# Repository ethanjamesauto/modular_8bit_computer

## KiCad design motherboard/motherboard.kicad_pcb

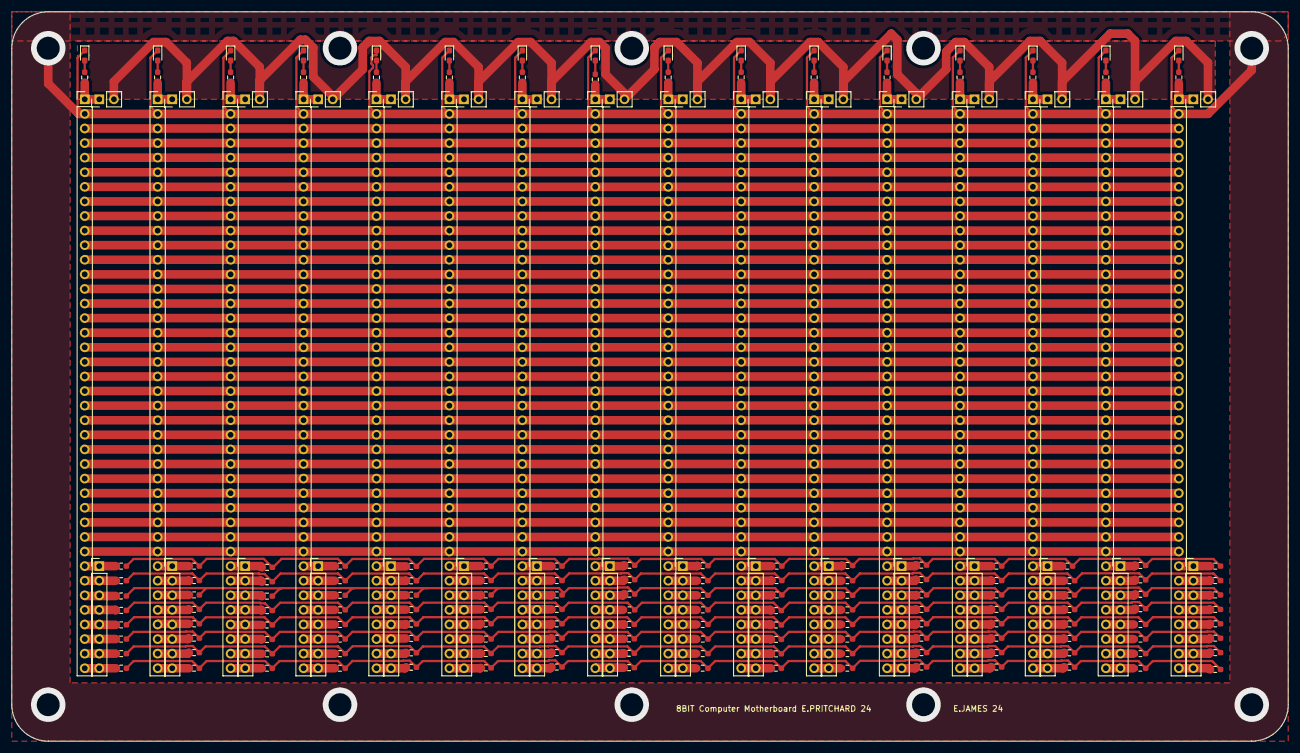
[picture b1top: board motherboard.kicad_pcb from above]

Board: 2 copper layers, 222.3 x 127.0 mm, 208 parts (0 on the bottom side), 200 nets.

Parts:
D1, D2, D3, D4, D5, D6, D7, D8, D9, D10, D11, D12, D13, D14, D15, D16: A0; LED_0603_1608Metric_Pad1.05x0.95mm_HandSolder
J1, J2, J5, J7, J9, J11, J13, J15, J17, J19, J21, J23, J25, J27, J29, J31: Conn_01x40_Pin; PinHeader_1x40_P2.54mm_Vertical
J3, J4, J6, J8, J10, J12, J14, J16, J18, J20, J22, J24, J26, J28, J30, J32: Conn_01x08_Pin; PinHeader_1x08_P2.54mm_Vertical
J33, J34, J35, J36, J37, J38, J39, J40, J41, J42, J43, J44, J45, J46, J47, J48: Conn_01x02_Pin; PinHeader_1x02_P2.54mm_Vertical
r1, r2, r3, r4, r5, r6, r7, r8, r9, r10, r11, r12, r13, r14, r15, r16, r17, r18, r19, r20, r21, r22, r23, r24, r25, r26, r27, r28, r29, r30, r31, r32, r33, r34, r35, r36, r37, r38, r39, r40, r41, r42, r43, r44, r45, r46, r47, r48, r49, r50, r51, r52, r53, r54, r55, r56, r57, r58, r59, r60, r61, r62, r63, r64, r65, r66, r67, r68, r69, r70, r71, r72, r73, r74, r75, r76, r77, r78, r79, r80, r81, r82, r83, r84, r85, r86, r87, r88, r89, r90, r91, r92, r93, r94, r95, r96, r97, r98, r99, r100, r101, r102, r103, r104, r105, r106, r107, r108, r109, r110, r111, r112, r113, r114, r115, r116, r117, r118, r119, r120, r121, r122, r123, r124, r125, r126, r127, r128, r129, r130, r131, r132, r133, r134, r135, r136, r137, r138, r139, r140, r141, r142, r143, r144: 470; R_0603_1608Metric_Pad0.98x0.95mm_HandSolder

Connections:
/5V_rawA: J2.1, J33.1, r1.2
/5V_rawB: J1.1, J34.1, r10.2
/5V_rawC: J5.1, J35.1, r19.2
/5V_rawD: J7.1, J36.1, r28.2
/5V_rawE: J9.1, J37.1, r37.2
/5V_rawF: J11.1, J38.1, r46.2
/5V_rawG: J13.1, J39.1, r55.2
/5V_rawH: J15.1, J40.1, r64.2
/5V_rawJ: J17.1, J41.1, r73.2
/5V_rawK: J19.1, J42.1, r82.2
/5V_rawL: J21.1, J43.1, r91.2
/5V_rawM: J23.1, J44.1, r100.2
/5V_rawN: J25.1, J45.1, r109.2
/5V_rawO: J27.1, J46.1, r118.2
/5V_rawP: J29.1, J47.1, r127.2
/5V_rawQ: J31.1, J48.1, r136.2
/A: J1.5, J2.5, J5.5, J7.5, J9.5, J11.5, J13.5, J15.5, J17.5, J19.5, J21.5, J23.5, J25.5, J27.5, J29.5, J31.5
/Addr_0_LSB: J1.17, J2.17, J5.17, J7.17, J9.17, J11.17, J13.17, J15.17, J17.17, J19.17, J21.17, J23.17, J25.17, J27.17, J29.17, J31.17
/Addr_1: J1.18, J2.18, J5.18, J7.18, J9.18, J11.18, J13.18, J15.18, J17.18, J19.18, J21.18, J23.18, J25.18, J27.18, J29.18, J31.18
/Addr_2: J1.19, J2.19, J5.19, J7.19, J9.19, J11.19, J13.19, J15.19, J17.19, J19.19, J21.19, J23.19, J25.19, J27.19, J29.19, J31.19
/Addr_3: J1.20, J2.20, J5.20, J7.20, J9.20, J11.20, J13.20, J15.20, J17.20, J19.20, J21.20, J23.20, J25.20, J27.20, J29.20, J31.20
/Addr_4: J1.21, J2.21, J5.21, J7.21, J9.21, J11.21, J13.21, J15.21, J17.21, J19.21, J21.21, J23.21, J25.21, J27.21, J29.21, J31.21
/Addr_5: J1.22, J2.22, J5.22, J7.22, J9.22, J11.22, J13.22, J15.22, J17.22, J19.22, J21.22, J23.22, J25.22, J27.22, J29.22, J31.22
/Addr_6: J1.23, J2.23, J5.23, J7.23, J9.23, J11.23, J13.23, J15.23, J17.23, J19.23, J21.23, J23.23, J25.23, J27.23, J29.23, J31.23
/Addr_7: J1.24, J2.24, J5.24, J7.24, J9.24, J11.24, J13.24, J15.24, J17.24, J19.24, J21.24, J23.24, J25.24, J27.24, J29.24, J31.24
/Addr_8: J1.25, J2.25, J5.25, J7.25, J9.25, J11.25, J13.25, J15.25, J17.25, J19.25, J21.25, J23.25, J25.25, J27.25, J29.25, J31.25
/Addr_9: J1.26, J2.26, J5.26, J7.26, J9.26, J11.26, J13.26, J15.26, J17.26, J19.26, J21.26, J23.26, J25.26, J27.26, J29.26, J31.26
/Addr_10: J1.27, J2.27, J5.27, J7.27, J9.27, J11.27, J13.27, J15.27, J17.27, J19.27, J21.27, J23.27, J25.27, J27.27, J29.27, J31.27
/Addr_11: J1.28, J2.28, J5.28, J7.28, J9.28, J11.28, J13.28, J15.28, J17.28, J19.28, J21.28, J23.28, J25.28, J27.28, J29.28, J31.28
/Addr_12: J1.29, J2.29, J5.29, J7.29, J9.29, J11.29, J13.29, J15.29, J17.29, J19.29, J21.29, J23.29, J25.29, J27.29, J29.29, J31.29
/Addr_13: J1.30, J2.30, J5.30, J7.30, J9.30, J11.30, J13.30, J15.30, J17.30, J19.30, J21.30, J23.30, J25.30, J27.30, J29.30, J31.30
/Addr_14: J1.31, J2.31, J5.31, J7.31, J9.31, J11.31, J13.31, J15.31, J17.31, J19.31, J21.31, J23.31, J25.31, J27.31, J29.31, J31.31
/Addr_15_MSB: J1.32, J2.32, J5.32, J7.32, J9.32, J11.32, J13.32, J15.32, J17.32, J19.32, J21.32, J23.32, J25.32, J27.32, J29.32, J31.32
/Aux_Bus_0_LSB: r2.1, r11.1, r20.1, r29.1, r38.1, r47.1, r56.1, r65.1, r74.1, r83.1, r92.1, r101.1, r110.1, r119.1, r128.1, r137.1
/Aux_Bus_1: r3.1, r12.1, r21.1, r30.1, r39.1, r48.1, r57.1, r66.1, r75.1, r84.1, r93.1, r102.1, r111.1, r120.1, r129.1, r138.1
/Aux_Bus_2: r4.1, r13.1, r22.1, r31.1, r40.1, r49.1, r58.1, r67.1, r76.1, r85.1, r94.1, r103.1, r112.1, r121.1, r130.1, r139.1
/Aux_Bus_3: r5.1, r14.1, r23.1, r32.1, r41.1, r50.1, r59.1, r68.1, r77.1, r86.1, r95.1, r104.1, r113.1, r122.1, r131.1, r140.1
/Aux_Bus_4: r6.1, r15.1, r24.1, r33.1, r42.1, r51.1, r60.1, r69.1, r78.1, r87.1, r96.1, r105.1, r114.1, r123.1, r132.1, r141.1
/Aux_Bus_5: r7.1, r16.1, r25.1, r34.1, r43.1, r52.1, r61.1, r70.1, r79.1, r88.1, r97.1, r106.1, r115.1, r124.1, r133.1, r142.1
/Aux_Bus_6: r8.1, r17.1, r26.1, r35.1, r44.1, r53.1, r62.1, r71.1, r80.1, r89.1, r98.1, r107.1, r116.1, r125.1, r134.1, r143.1
/Aux_Bus_7_MSB: r9.1, r18.1, r27.1, r36.1, r45.1, r54.1, r63.1, r72.1, r81.1, r90.1, r99.1, r108.1, r117.1, r126.1, r135.1, r144.1
/B: J1.6, J2.6, J5.6, J7.6, J9.6, J11.6, J13.6, J15.6, J17.6, J19.6, J21.6, J23.6, J25.6, J27.6, J29.6, J31.6
/C: J1.7, J2.7, J5.7, J7.7, J9.7, J11.7, J13.7, J15.7, J17.7, J19.7, J21.7, J23.7, J25.7, J27.7, J29.7, J31.7
/D: J1.8, J2.8, J5.8, J7.8, J9.8, J11.8, J13.8, J15.8, J17.8, J19.8, J21.8, J23.8, J25.8, J27.8, J29.8, J31.8
/Data_Bus_0_LSB: J1.9, J2.9, J5.9, J7.9, J9.9, J11.9, J13.9, J15.9, J17.9, J19.9, J21.9, J23.9, J25.9, J27.9, J29.9, J31.9
/Data_Bus_1: J1.10, J2.10, J5.10, J7.10, J9.10, J11.10, J13.10, J15.10, J17.10, J19.10, J21.10, J23.10, J25.10, J27.10, J29.10, J31.10
/Data_Bus_2: J1.11, J2.11, J5.11, J7.11, J9.11, J11.11, J13.11, J15.11, J17.11, J19.11, J21.11, J23.11, J25.11, J27.11, J29.11, J31.11
/Data_Bus_3: J1.12, J2.12, J5.12, J7.12, J9.12, J11.12, J13.12, J15.12, J17.12, J19.12, J21.12, J23.12, J25.12, J27.12, J29.12, J31.12
/Data_Bus_4: J1.13, J2.13, J5.13, J7.13, J9.13, J11.13, J13.13, J15.13, J17.13, J19.13, J21.13, J23.13, J25.13, J27.13, J29.13, J31.13
/Data_Bus_5: J1.14, J2.14, J5.14, J7.14, J9.14, J11.14, J13.14, J15.14, J17.14, J19.14, J21.14, J23.14, J25.14, J27.14, J29.14, J31.14
/Data_Bus_6: J1.15, J2.15, J5.15, J7.15, J9.15, J11.15, J13.15, J15.15, J17.15, J19.15, J21.15, J23.15, J25.15, J27.15, J29.15, J31.15
/Data_Bus_7_MSB: J1.16, J2.16, J5.16, J7.16, J9.16, J11.16, J13.16, J15.16, J17.16, J19.16, J21.16, J23.16, J25.16, J27.16, J29.16, J31.16
/clk: J1.3, J2.3, J5.3, J7.3, J9.3, J11.3, J13.3, J15.3, J17.3, J19.3, J21.3, J23.3, J25.3, J27.3, J29.3, J31.3
/reset_n: J1.4, J2.4, J5.4, J7.4, J9.4, J11.4, J13.4, J15.4, J17.4, J19.4, J21.4, J23.4, J25.4, J27.4, J29.4, J31.4
GND: D1.1 (K), D2.1 (K), D3.1 (K), D4.1 (K), D5.1 (K), D6.1 (K), D7.1 (K), D8.1 (K), D9.1 (K), D10.1 (K), D11.1 (K), D12.1 (K), D13.1 (K), D14.1 (K), D15.1 (K), D16.1 (K), J1.2, J2.2, J5.2, J7.2, J9.2, J11.2, J13.2, J15.2, J17.2, J19.2, J21.2, J23.2, J25.2, J27.2, J29.2, J31.2
unnamed: D1.2 (A), r1.1
unnamed: D2.2 (A), r10.1
unnamed: D3.2 (A), r19.1
unnamed: D4.2 (A), r28.1
unnamed: D5.2 (A), r37.1
unnamed: D6.2 (A), r46.1
unnamed: D7.2 (A), r55.1
unnamed: D8.2 (A), r64.1
unnamed: D9.2 (A), r73.1
unnamed: D10.2 (A), r82.1
unnamed: D11.2 (A), r91.1
unnamed: D12.2 (A), r100.1
unnamed: D13.2 (A), r109.1
unnamed: D14.2 (A), r118.1
unnamed: D15.2 (A), r127.1
unnamed: D16.2 (A), r136.1
unnamed: J1.33, J3.1, r11.2
unnamed: J1.34, J3.2, r12.2
unnamed: J1.35, J3.3, r13.2
unnamed: J1.36, J3.4, r14.2
unnamed: J1.37, J3.5, r15.2
unnamed: J1.38, J3.6, r16.2
unnamed: J1.39, J3.7, r17.2
unnamed: J1.40, J3.8, r18.2
unnamed: J2.33, J4.1, r2.2
unnamed: J2.34, J4.2, r3.2
unnamed: J2.35, J4.3, r4.2
unnamed: J2.36, J4.4, r5.2
unnamed: J2.37, J4.5, r6.2
unnamed: J2.38, J4.6, r7.2
unnamed: J2.39, J4.7, r8.2
unnamed: J2.40, J4.8, r9.2
unnamed: J5.33, J6.1, r20.2
unnamed: J5.34, J6.2, r21.2
unnamed: J5.35, J6.3, r22.2
unnamed: J5.36, J6.4, r23.2
unnamed: J5.37, J6.5, r24.2
unnamed: J5.38, J6.6, r25.2
unnamed: J5.39, J6.7, r26.2
unnamed: J5.40, J6.8, r27.2
unnamed: J7.33, J8.1, r29.2
unnamed: J7.34, J8.2, r30.2
unnamed: J7.35, J8.3, r31.2
unnamed: J7.36, J8.4, r32.2
unnamed: J7.37, J8.5, r33.2
unnamed: J7.38, J8.6, r34.2
unnamed: J7.39, J8.7, r35.2
unnamed: J7.40, J8.8, r36.2
unnamed: J9.33, J10.1, r38.2
unnamed: J9.34, J10.2, r39.2
unnamed: J9.35, J10.3, r40.2
unnamed: J9.36, J10.4, r41.2
unnamed: J9.37, J10.5, r42.2
unnamed: J9.38, J10.6, r43.2
unnamed: J9.39, J10.7, r44.2
unnamed: J9.40, J10.8, r45.2
unnamed: J11.33, J12.1, r47.2
unnamed: J11.34, J12.2, r48.2
unnamed: J11.35, J12.3, r49.2
unnamed: J11.36, J12.4, r50.2
unnamed: J11.37, J12.5, r51.2
unnamed: J11.38, J12.6, r52.2
unnamed: J11.39, J12.7, r53.2
unnamed: J11.40, J12.8, r54.2
unnamed: J13.33, J14.1, r56.2
unnamed: J13.34, J14.2, r57.2
unnamed: J13.35, J14.3, r58.2
unnamed: J13.36, J14.4, r59.2
unnamed: J13.37, J14.5, r60.2
unnamed: J13.38, J14.6, r61.2
unnamed: J13.39, J14.7, r62.2
unnamed: J13.40, J14.8, r63.2
unnamed: J15.33, J16.1, r65.2
unnamed: J15.34, J16.2, r66.2
unnamed: J15.35, J16.3, r67.2
unnamed: J15.36, J16.4, r68.2
unnamed: J15.37, J16.5, r69.2
unnamed: J15.38, J16.6, r70.2
unnamed: J15.39, J16.7, r71.2
unnamed: J15.40, J16.8, r72.2
unnamed: J17.33, J18.1, r74.2
unnamed: J17.34, J18.2, r75.2
unnamed: J17.35, J18.3, r76.2
unnamed: J17.36, J18.4, r77.2
unnamed: J17.37, J18.5, r78.2
unnamed: J17.38, J18.6, r79.2
unnamed: J17.39, J18.7, r80.2
unnamed: J17.40, J18.8, r81.2
unnamed: J19.33, J20.1, r83.2
unnamed: J19.34, J20.2, r84.2
unnamed: J19.35, J20.3, r85.2
unnamed: J19.36, J20.4, r86.2
unnamed: J19.37, J20.5, r87.2
unnamed: J19.38, J20.6, r88.2
unnamed: J19.39, J20.7, r89.2
unnamed: J19.40, J20.8, r90.2
unnamed: J21.33, J22.1, r92.2
unnamed: J21.34, J22.2, r93.2
unnamed: J21.35, J22.3, r94.2
unnamed: J21.36, J22.4, r95.2
unnamed: J21.37, J22.5, r96.2
unnamed: J21.38, J22.6, r97.2
unnamed: J21.39, J22.7, r98.2
unnamed: J21.40, J22.8, r99.2
unnamed: J23.33, J24.1, r101.2
unnamed: J23.34, J24.2, r102.2
unnamed: J23.35, J24.3, r103.2
unnamed: J23.36, J24.4, r104.2
unnamed: J23.37, J24.5, r105.2
unnamed: J23.38, J24.6, r106.2
unnamed: J23.39, J24.7, r107.2
unnamed: J23.40, J24.8, r108.2
unnamed: J25.33, J26.1, r110.2
unnamed: J25.34, J26.2, r111.2
unnamed: J25.35, J26.3, r112.2
unnamed: J25.36, J26.4, r113.2
unnamed: J25.37, J26.5, r114.2
unnamed: J25.38, J26.6, r115.2
unnamed: J25.39, J26.7, r116.2
unnamed: J25.40, J26.8, r117.2
unnamed: J27.33, J28.1, r119.2
unnamed: J27.34, J28.2, r120.2
unnamed: J27.35, J28.3, r121.2
unnamed: J27.36, J28.4, r122.2
unnamed: J27.37, J28.5, r123.2
unnamed: J27.38, J28.6, r124.2
unnamed: J27.39, J28.7, r125.2
unnamed: J27.40, J28.8, r126.2
unnamed: J29.33, J30.1, r128.2
unnamed: J29.34, J30.2, r129.2
unnamed: J29.35, J30.3, r130.2
unnamed: J29.36, J30.4, r131.2
unnamed: J29.37, J30.5, r132.2
unnamed: J29.38, J30.6, r133.2
unnamed: J29.39, J30.7, r134.2
unnamed: J29.40, J30.8, r135.2
unnamed: J31.33, J32.1, r137.2
unnamed: J31.34, J32.2, r138.2
unnamed: J31.35, J32.3, r139.2
unnamed: J31.36, J32.4, r140.2
unnamed: J31.37, J32.5, r141.2
unnamed: J31.38, J32.6, r142.2
unnamed: J31.39, J32.7, r143.2
unnamed: J31.40, J32.8, r144.2
VCC: J33.2, J34.2, J35.2, J36.2, J37.2, J38.2, J39.2, J40.2, J41.2, J42.2, J43.2, J44.2, J45.2, J46.2, J47.2, J48.2

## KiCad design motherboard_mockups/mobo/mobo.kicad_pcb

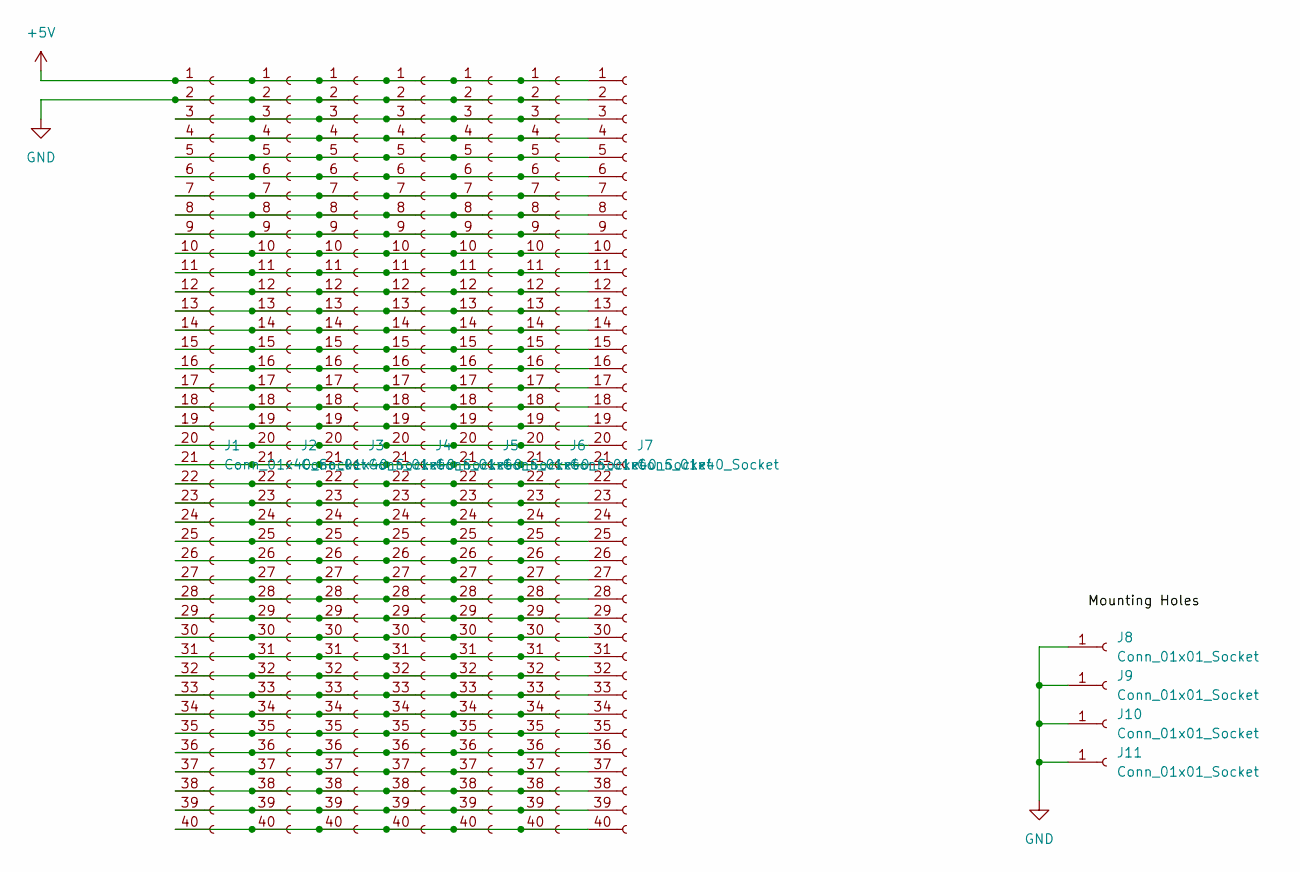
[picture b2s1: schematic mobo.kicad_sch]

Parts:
J1, J2, J3, J4, J5, J6, J7: Conn_01x40_Socket; PinSocket_1x40_P2.54mm_Vertical
J8: Conn_01x01_Socket; MountingHole_4.3mm_M4_ISO7380_Pad
J9, J10, J11: Conn_01x01_Socket; MountingHole_4.3mm_M4_DIN965_Pad

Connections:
+5V: J1.1, J2.1, J3.1, J4.1, J5.1, J6.1, J7.1
GND: J1.2, J2.2, J3.2, J4.2, J5.2, J6.2, J7.2, J8.1, J9.1, J10.1, J11.1
unnamed: J1.3, J2.3, J3.3, J4.3, J5.3, J6.3, J7.3
unnamed: J1.4, J2.4, J3.4, J4.4, J5.4, J6.4, J7.4
unnamed: J1.5, J2.5, J3.5, J4.5, J5.5, J6.5, J7.5
unnamed: J1.6, J2.6, J3.6, J4.6, J5.6, J6.6, J7.6
unnamed: J1.7, J2.7, J3.7, J4.7, J5.7, J6.7, J7.7
unnamed: J1.8, J2.8, J3.8, J4.8, J5.8, J6.8, J7.8
unnamed: J1.9, J2.9, J3.9, J4.9, J5.9, J6.9, J7.9
unnamed: J1.10, J2.10, J3.10, J4.10, J5.10, J6.10, J7.10
unnamed: J1.11, J2.11, J3.11, J4.11, J5.11, J6.11, J7.11
unnamed: J1.12, J2.12, J3.12, J4.12, J5.12, J6.12, J7.12
unnamed: J1.13, J2.13, J3.13, J4.13, J5.13, J6.13, J7.13
unnamed: J1.14, J2.14, J3.14, J4.14, J5.14, J6.14, J7.14
unnamed: J1.15, J2.15, J3.15, J4.15, J5.15, J6.15, J7.15
unnamed: J1.16, J2.16, J3.16, J4.16, J5.16, J6.16, J7.16
unnamed: J1.17, J2.17, J3.17, J4.17, J5.17, J6.17, J7.17
unnamed: J1.18, J2.18, J3.18, J4.18, J5.18, J6.18, J7.18
unnamed: J1.19, J2.19, J3.19, J4.19, J5.19, J6.19, J7.19
unnamed: J1.20, J2.20, J3.20, J4.20, J5.20, J6.20, J7.20
unnamed: J1.21, J2.21, J3.21, J4.21, J5.21, J6.21, J7.21
unnamed: J1.22, J2.22, J3.22, J4.22, J5.22, J6.22, J7.22
unnamed: J1.23, J2.23, J3.23, J4.23, J5.23, J6.23, J7.23
unnamed: J1.24, J2.24, J3.24, J4.24, J5.24, J6.24, J7.24
unnamed: J1.25, J2.25, J3.25, J4.25, J5.25, J6.25, J7.25
unnamed: J1.26, J2.26, J3.26, J4.26, J5.26, J6.26, J7.26
unnamed: J1.27, J2.27, J3.27, J4.27, J5.27, J6.27, J7.27
unnamed: J1.28, J2.28, J3.28, J4.28, J5.28, J6.28, J7.28
unnamed: J1.29, J2.29, J3.29, J4.29, J5.29, J6.29, J7.29
unnamed: J1.30, J2.30, J3.30, J4.30, J5.30, J6.30, J7.30
unnamed: J1.31, J2.31, J3.31, J4.31, J5.31, J6.31, J7.31
unnamed: J1.32, J2.32, J3.32, J4.32, J5.32, J6.32, J7.32
unnamed: J1.33, J2.33, J3.33, J4.33, J5.33, J6.33, J7.33
unnamed: J1.34, J2.34, J3.34, J4.34, J5.34, J6.34, J7.34
unnamed: J1.35, J2.35, J3.35, J4.35, J5.35, J6.35, J7.35
unnamed: J1.36, J2.36, J3.36, J4.36, J5.36, J6.36, J7.36
unnamed: J1.37, J2.37, J3.37, J4.37, J5.37, J6.37, J7.37
unnamed: J1.38, J2.38, J3.38, J4.38, J5.38, J6.38, J7.38
unnamed: J1.39, J2.39, J3.39, J4.39, J5.39, J6.39, J7.39
unnamed: J1.40, J2.40, J3.40, J4.40, J5.40, J6.40, J7.40

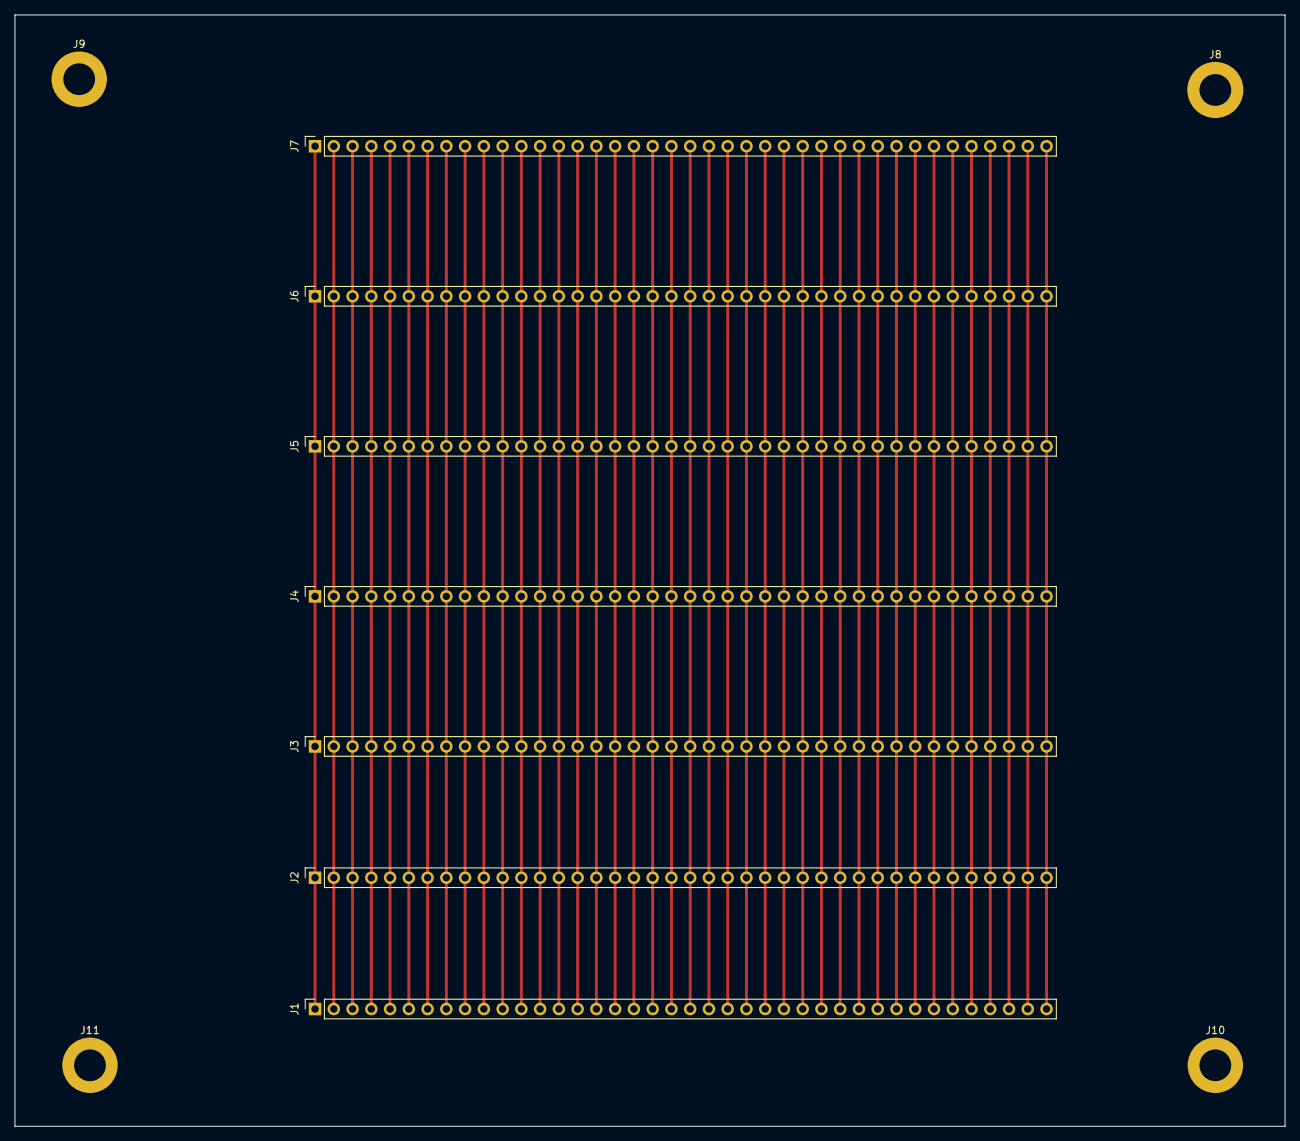
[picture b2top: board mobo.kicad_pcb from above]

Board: 2 copper layers, 172.0 x 150.5 mm, 11 parts (0 on the bottom side), 40 nets.

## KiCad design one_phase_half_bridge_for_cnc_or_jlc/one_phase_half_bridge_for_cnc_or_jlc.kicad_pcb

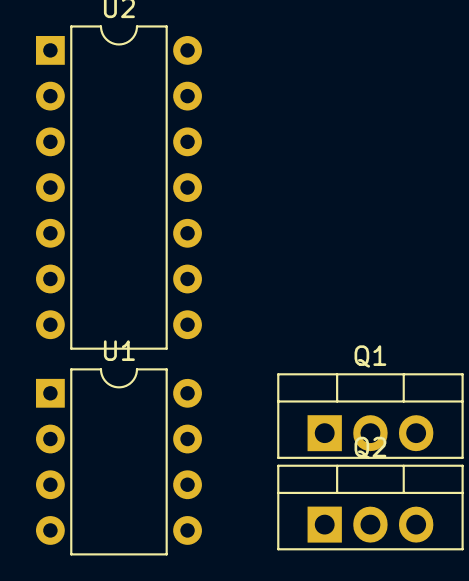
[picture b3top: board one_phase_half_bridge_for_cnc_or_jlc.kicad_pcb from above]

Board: 2 copper layers, 4 parts (0 on the bottom side), 2 nets, no tracks yet.

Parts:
Q1, Q2: NMOS; TO-220-3_Vertical
U1: IR2104; DIP-8_W7.62mm
U2: 74LS00; DIP-14_W7.62mm

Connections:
/sw_node: Q1.3 (S), Q2.1 (D), U1.6 (VS)
GND: Q2.3 (S), U1.4 (COM)

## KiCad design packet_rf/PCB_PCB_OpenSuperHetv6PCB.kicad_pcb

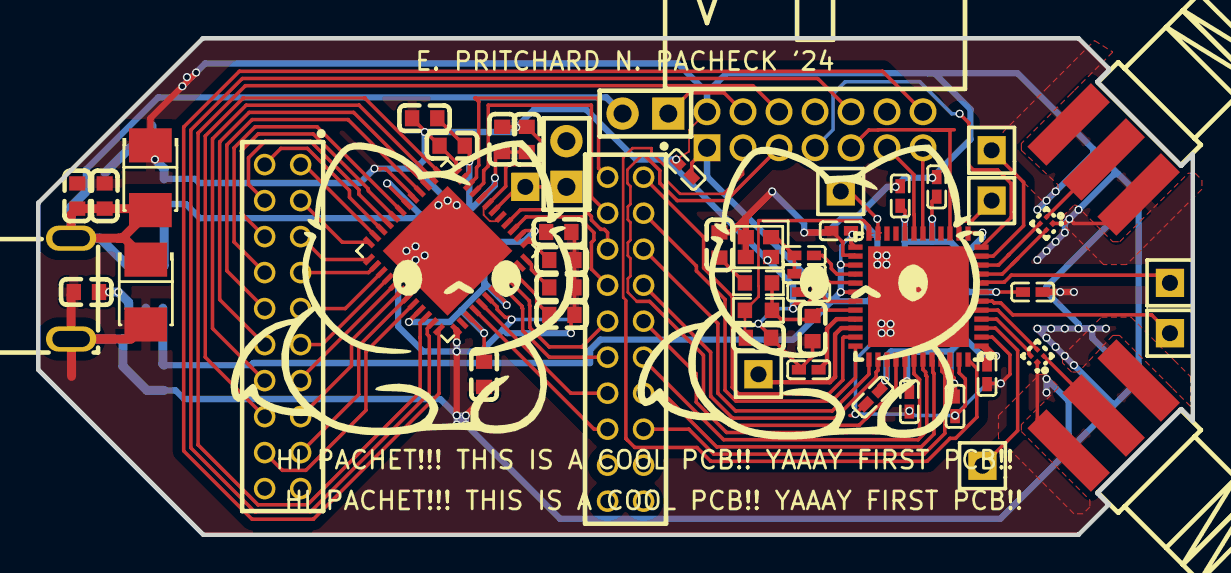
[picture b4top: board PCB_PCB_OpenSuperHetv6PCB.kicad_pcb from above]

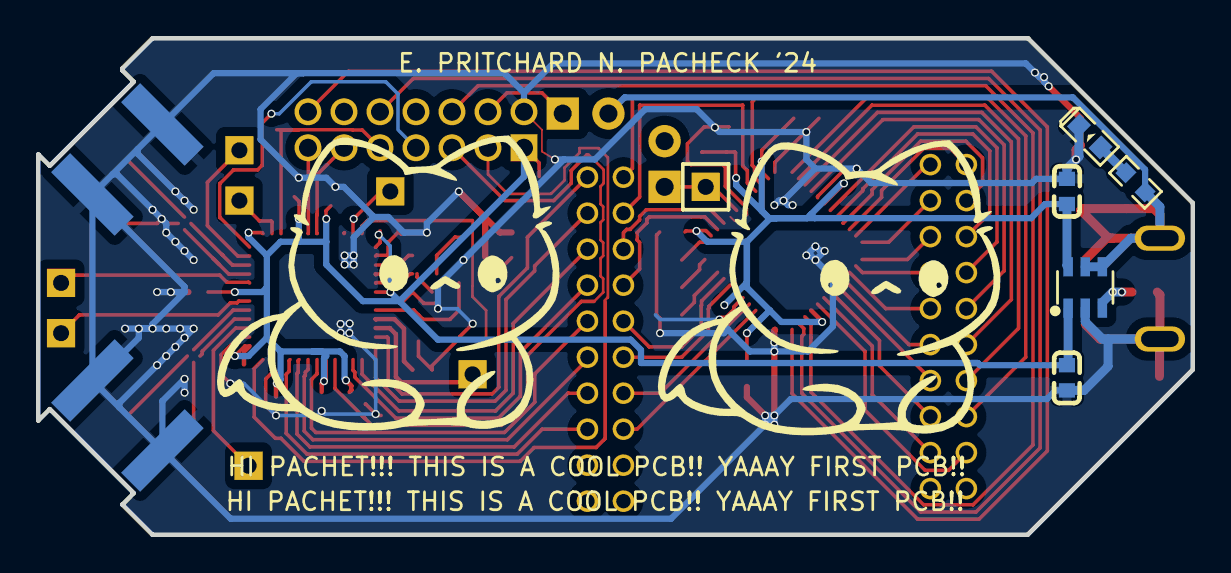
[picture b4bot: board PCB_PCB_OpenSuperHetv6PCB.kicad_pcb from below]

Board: 2 copper layers, 64.1 x 27.6 mm, 58 parts (8 on the bottom side), 74 nets.

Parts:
ANT_BALUN1, ANT_BALUN2: 50TO100ohm; XFMR-SMD_4P-L1.1-W1.1-P0.50-BL
ANT_SMA1, ANT_SMA2: HX-SMA-P-9631; RF-SMA-SMD_HX-SMA-P-9631
C1, C2, C8, C9, C10, C11, C12, C13: 0.1u; C0402
C3: 1000pF; C0402
C4: 33pF; C0402
C5: 18pF; C0402
C6: 10uF; C0402
C7: 100pF; C0402
C14, C33, C36: 100nF; C0603
C15, C16: 10uF; CAP-SMD_L3.5-W2.8-FD
C19, C20: .33uF; C0603
C21: 100pF; C0603
C22: 2200pF; C0603
C23: 68pF; C0603
C24: .1uF; C0603
C26, C27, C29, C31, C37, C39, C41: 2.2uF; C0603
C35: 10nF; C0603
CLK1: HDR-M-2.54_1x1; HDR-M-2.54_1X1
DC1: DC-047B-13A; DC-IN-TH_DC-047B-13A
J1, J2, J3, J4, J5, J6, J7: HDR-M-2.54_1x1; HDR-M-2.54_1X1
LED1: LED-0603_R; LED0603_RED
R1: 1.2k; R0603
R2: 750pF; R0603
R3: 1k; R0603
SYS_CTRL: A2005WR-N-2X7P-B; CONN-TH_A2005WR-N-2X7P-B
U1: MAX5864ETM+; QFN-48_L7.0-W7.0-P0.50-BL-EP5.1
U2, U3: 2×10CH2.0; CONN-TH_2X10P-P2.00_KINGHELM_KH-2FH-2X10P-H4.3
U4: MAX8882EUTJJ; SOT-23-6_L2.9-W1.6-P0.95-LS2.8-BL
U5: -; TQFN-48_L7.0-W7.0-P0.50-TL-EP5.6
U6, U7: JUMPER2; HDR-TH_2P-P2.54-V-M-1
X3: 40MHz; CRYSTAL-SMD_4P-L2.0-W1.6-BL

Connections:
+5V: C14.2, C15.1, C16.2, C36.2, DC1.1, R3.1, U4.4, U4.5, U7.2
ADC_OUT0: U1.13, U3.16
ADC_OUT1: U1.14, U3.14
ADC_OUT2: U1.15, U3.12
ADC_OUT3: U1.16, U3.10
ADC_OUT4: U1.19, U3.8
ADC_OUT5: U1.20, U3.6
ADC_OUT6: U1.21, U3.4
ADC_OUT7: U1.22, U3.2
ANT_BALUN2_2: ANT_BALUN2.2, ANT_SMA2.5
ANT_BALUN2_3: ANT_BALUN2.3, U5.10
ANT_BALUN2_4: ANT_BALUN2.4, U5.9
ANT_SMA1_5: ANT_BALUN1.2, ANT_SMA1.5
BBC_CLK: CLK1.1, U1.6, U6.1
BBC_CS: SYS_CTRL.14, U1.36
BBC_DIN: SYS_CTRL.6, U1.34
BBC_SCLK: SYS_CTRL.10, U1.35
C22_2: C22.2, R1.1
C23_2: C23.2, R2.1, U5.24
DAC_IN0: U1.23, U3.1
DAC_IN1: U1.24, U3.3
DAC_IN2: U1.25, U3.5
DAC_IN3: U1.26, U3.7
DAC_IN4: U1.27, U3.9
DAC_IN5: U1.28, U3.11
DAC_IN6: U1.29, U3.13
DAC_IN7: U1.30, U3.15
DAC_IN8: U1.31, U3.17
DAC_IN9: U1.32, U3.18
DB1: J7.1, U5.23
DB2: J6.1, U5.11
DB3: J5.1, U5.8
DB4: J4.1, U5.34
DB5: J3.1, U5.14
DB6: J2.1, U5.3
DB7: J1.1, U5.6
ELPOUT: C21.2, R1.2, R2.2, U5.32
GND: ANT_BALUN1.1, ANT_BALUN2.1, ANT_SMA1.1, ANT_SMA1.2, ANT_SMA1.3, ANT_SMA1.4, ANT_SMA2.1, ANT_SMA2.2, ANT_SMA2.3, ANT_SMA2.4, C1.1, C2.2, C5.1, C6.2, C7.2, C8.1, C9.1, C10.1, C11.1, C12.1, C13.1, C14.1, C15.2, C16.1, C19.2, C20.2, C21.1, C22.1, C23.1, C24.2, C26.1, C27.1, C29.1, C31.1, C33.1, C35.1, C36.1, C37.1, C39.1, C41.1, DC1.2, LED1.2, SYS_CTRL.2, U1.5, U1.7, U1.12, U1.17, U1.37, U1.42, U1.49, U4.2, U5.2, U5.26, U5.31, U5.47, U5.49, X3.2, X3.3, X3.4
LED1_1: LED1.1, R3.2
RXTX_MODE: SYS_CTRL.3, U5.48
RX_BBIN: U2.5, U5.37
RX_BBIN_FEEDBACK: U1.4, U2.6
RX_BBIP: U2.7, U5.38
RX_BBIP_FEEDBACK: U1.3, U2.8
RX_BBQN: U2.1, U5.35
RX_BBQN_FEEDBACK: U1.9, U2.4
RX_BBQP: U2.3, U5.36
RX_BBQP_FEEDBACK: U1.10, U2.2
RX_HP_CTRL: SYS_CTRL.5, U5.40
TR_CS#: SYS_CTRL.9, U5.15
TR_DIN: SYS_CTRL.11, U5.19
TR_SCLK: SYS_CTRL.13, U5.18
TR_SHDN#: SYS_CTRL.7, U5.12
TX_BBIN: U1.44, U2.12
TX_BBIN_FEEDBACK: U2.13, U5.44
TX_BBIP: U1.45, U2.10
TX_BBIP_FEEDBACK: U2.15, U5.45
TX_BBQN: U1.41, U2.14
TX_BBQN_FEEDBACK: U2.9, U5.42
TX_BBQP: U1.40, U2.16
TX_BBQP_FEEDBACK: U2.11, U5.43
U1_1: C19.1, U1.1
U1_46: C24.1, U1.46
U1_48: C20.1, U1.48
U4_3: C35.2, U4.3
U5_4: ANT_BALUN1.4, U5.4
U5_5: ANT_BALUN1.3, U5.5
U5_28: C3.1, U5.28
U5_29: C4.2, C5.2, U5.29
U5_33: C2.1, U5.33
U7_1: SYS_CTRL.4, U7.1
VCC: C1.2, C6.1, C7.1, C8.2, C9.2, C10.2, C11.2, C12.2, C13.2, C33.2, SYS_CTRL.1, U4.1, U5.1, U5.7, U5.13, U5.17, U5.20, U5.25, U5.27, U5.30, U5.39, U5.41, U5.46
VCCDAC: C26.2, C27.2, C29.2, C31.2, C37.2, C39.2, C41.2, U1.2, U1.8, U1.11, U1.18, U1.33, U1.39, U1.43, U4.6
X3_1: C3.2, C4.1, X3.1
